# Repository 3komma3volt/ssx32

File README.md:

# ssx32
Open source servo controller
using a PIC18F46K20

software by Michael Bradley http://www.mculabs.com/projects/ssx32.html

hardware by berndp using Eagle 7.0 Freeware

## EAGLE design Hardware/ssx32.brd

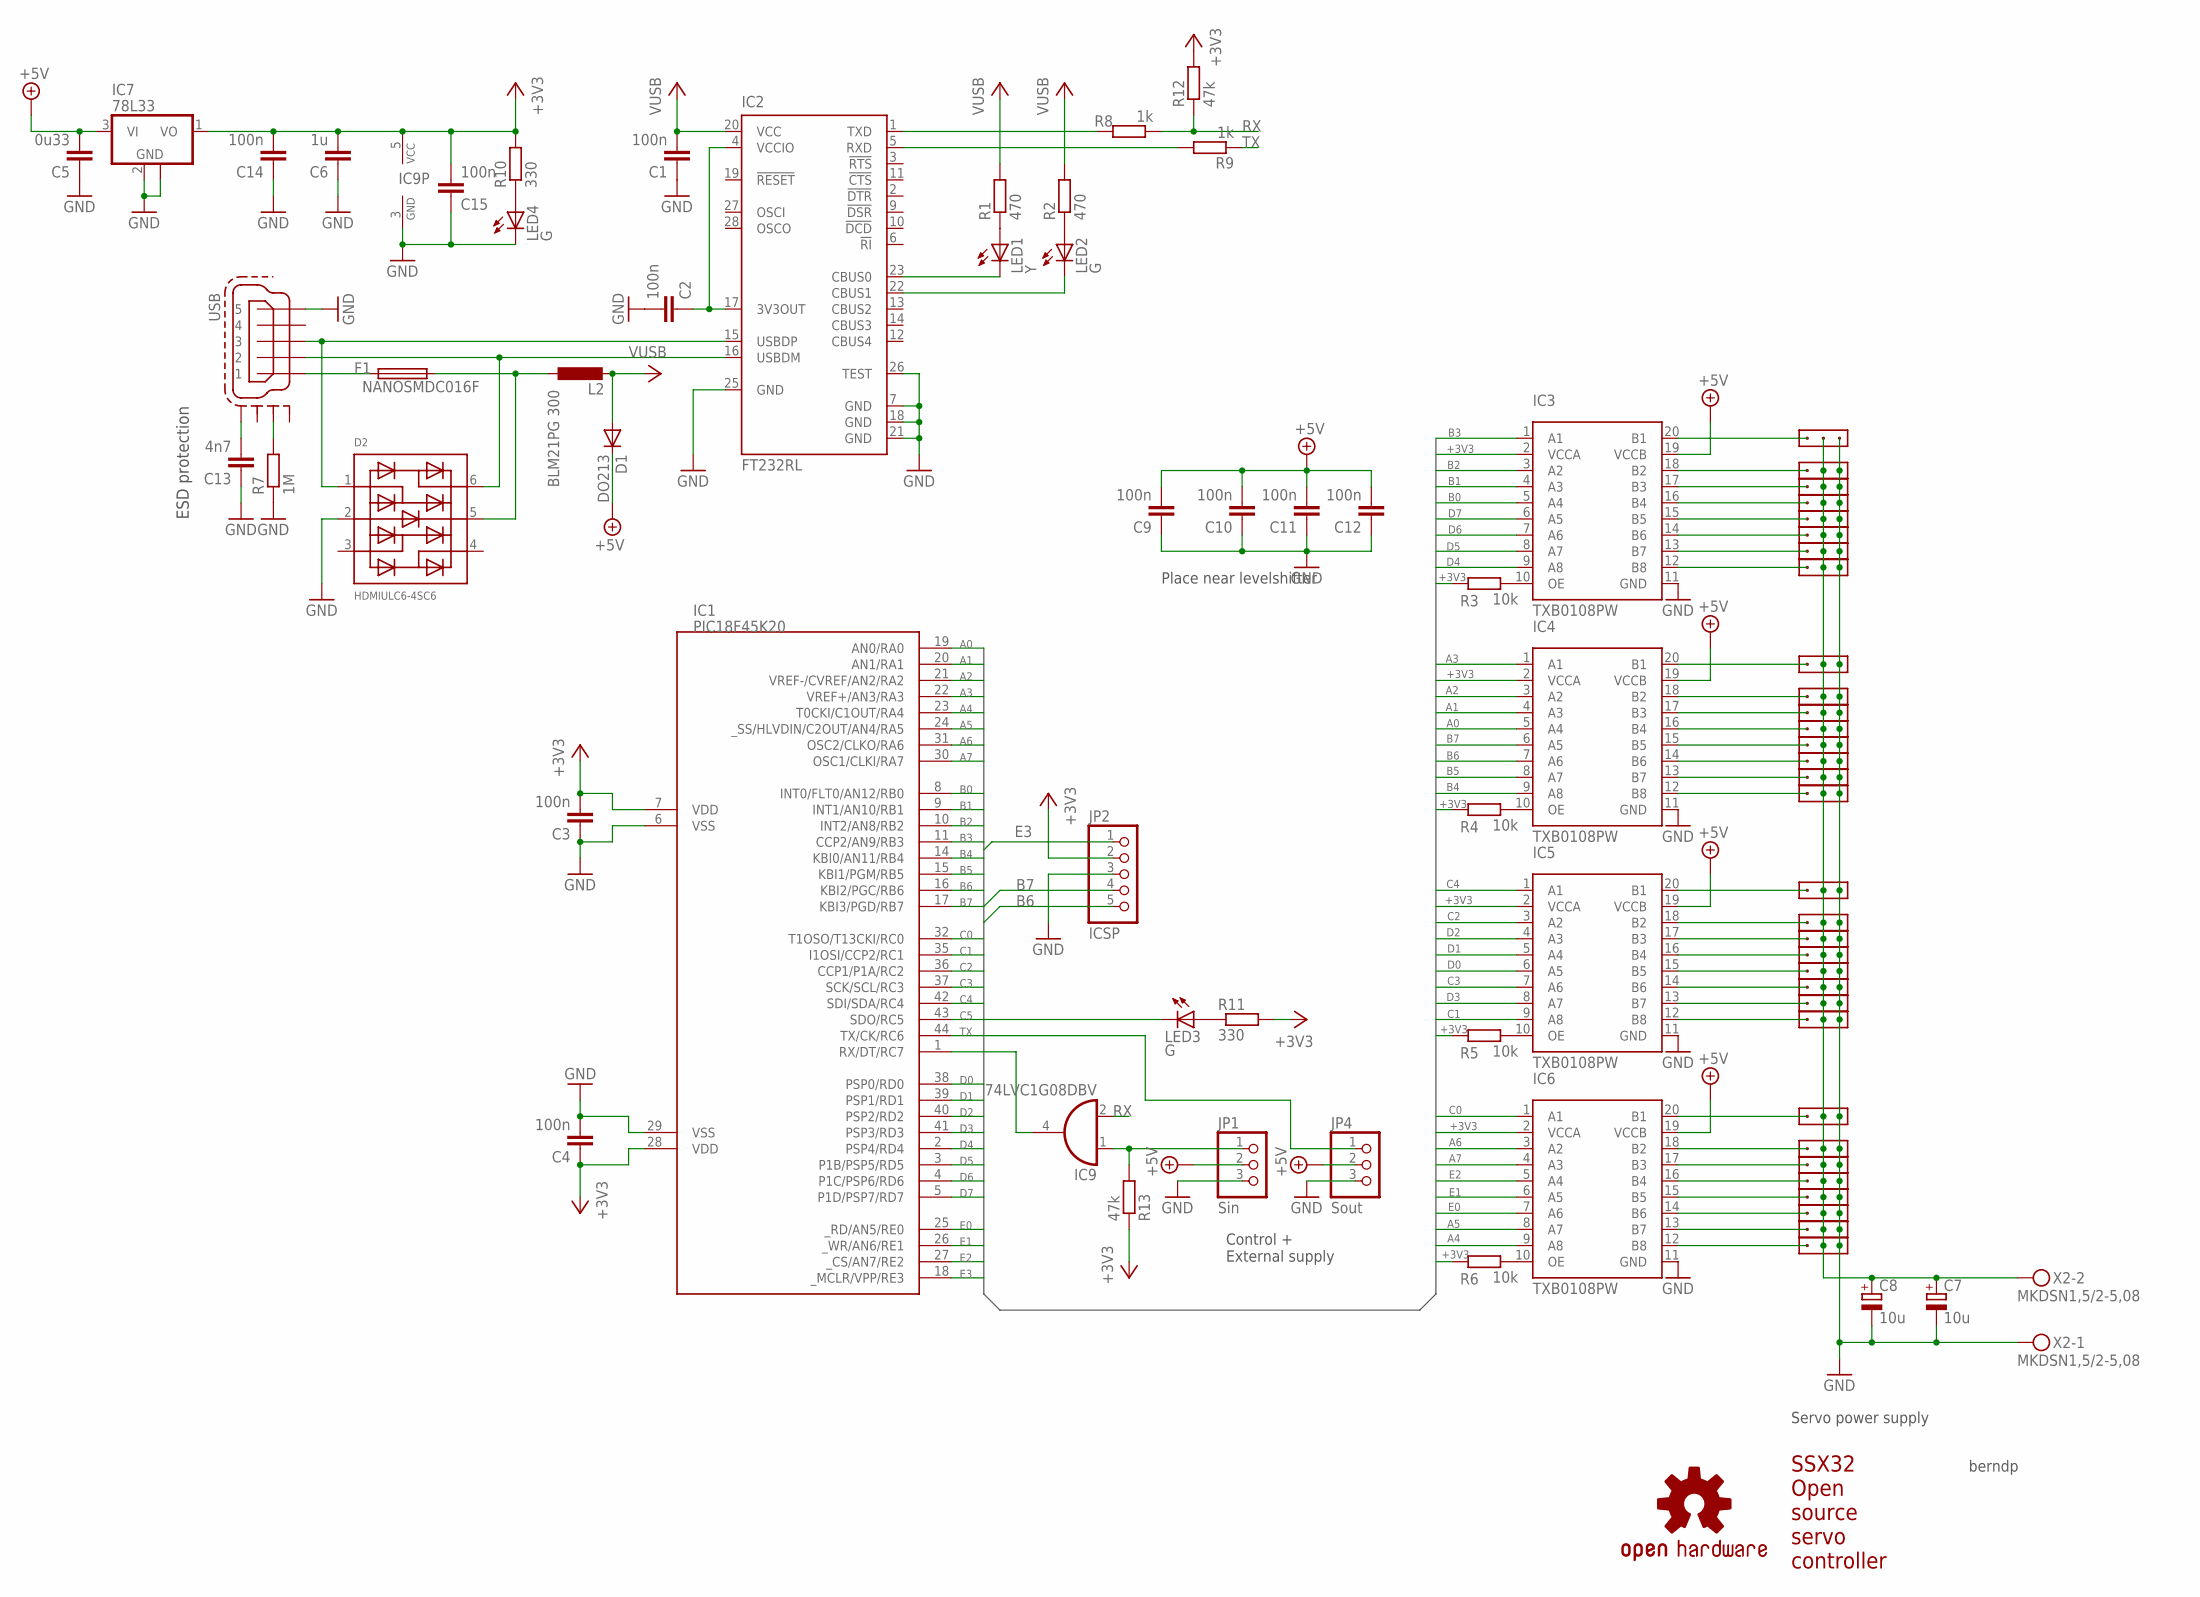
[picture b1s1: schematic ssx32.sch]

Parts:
C1, C2, C3, C4, C9, C10, C11, C12, C14, C15: 100n; C0603
C5: 0u33; C0805
C6: 1u; C0603
C7, C8: 10u; 153CLV-0505
C13: 4n7; C0603
D1: DO213; MINIMELF
D2: HDMIULC6-4SC6; SOT23-5
F1: NANOSMDC016F
IC1: PIC18F45K20; PIC18FXX20_TQFP44
IC2: FT232RL; SSOP28
IC3, IC4, IC5, IC6: TXB0108PW; PW_R-PDSO-G20
IC7: 78L33; SOT89
IC9: 74LVC1G08DBV; SOT23-5
JP1: Sin; 1X03
JP2: ICSP; 1X05
JP4: Sout; 1X03
L2: BLM21PG 300; R0805
LED1: Y; CHIPLED_0603
LED2, LED3, LED4: G; CHIPLED_0603
R1, R2: 470; R0603
R3, R4, R5, R6: 10k; R0603
R7: 1M; R0603
R8, R9: 1k; R0603
R10, R11: 330; R0603
R12, R13: 47k; R0603
U$2: OSHW-LOGOM; OSHW-LOGO-M
X1: 8; 1X3
X2: MKDSN1,5/2-5,08
X3: 17; 1X3
X4: 7; 1X3
X5: 6; 1X3
X6: 5; 1X3
X7: 4; 1X3
X8: 3; 1X3
X9: 2; 1X3
X10: 1; 1X3
X11: 19; 1X3
X12: 16; 1X3
X13: 15; 1X3
X14: 14; 1X3
X15: 13; 1X3
X16: 12; 1X3
X17: 11; 1X3
X18: 10; 1X3
X19: 9; 1X3
X20: 20; 1X3
X21: 21; 1X3
X22: 22; 1X3
X23: 23; 1X3
X24: 24; 1X3
X25: 25; 1X3
X26: 26; 1X3
X27: 27; 1X3
X28: 28; 1X3
X29: 29; 1X3
X30: 30; 1X3
X31: 31; 1X3
X32: 32; 1X3
X34: 18; 1X3
X35: USB; 32005-301

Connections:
+3V3: C3.2, C4.1, C6.2, C14.2, C15.2, IC1.7 (VDD), IC1.28 (VDD), IC3.2 (VCCA), IC4.2 (VCCA), IC5.2 (VCCA), IC6.2 (VCCA), IC7.1 (VO), IC9.5 (VCC), JP2.2, R3.1, R4.1, R5.1, R6.1, R10.2, R11.2, R12.2, R13.1
+5V: C1.2, D1.A, IC2.20 (VCC), L2.2, R1.2, R2.2
+UB: C5.2, C9.2, C10.2, C11.2, C12.2, D1.C, IC3.19 (VCCB), IC4.19 (VCCB), IC5.19 (VCCB), IC6.19 (VCCB), IC7.3 (VI), JP1.2, JP4.2
A0: IC1.19 (AN0/RA0), IC4.5 (A4)
A1: IC1.20 (AN1/RA1), IC4.4 (A3)
A2: IC1.21 (VREF-/CVREF/AN2/RA2), IC4.3 (A2)
A3: IC1.22 (VREF+/AN3/RA3), IC4.1 (A1)
A4: IC1.23 (T0CKI/C1OUT/RA4), IC6.9 (A8)
A5: IC1.24 (_SS/HLVDIN/C2OUT/AN4/RA5), IC6.8 (A7)
A6: IC1.31 (OSC2/CLKO/RA6), IC6.3 (A2)
A7: IC1.30 (OSC1/CLKI/RA7), IC6.4 (A3)
B0: IC1.8 (INT0/FLT0/AN12/RB0), IC3.5 (A4)
B1: IC1.9 (INT1/AN10/RB1), IC3.4 (A3)
B2: IC1.10 (INT2/AN8/RB2), IC3.3 (A2)
B3: IC1.11 (CCP2/AN9/RB3), IC3.1 (A1)
B4: IC1.14 (KBI0/AN11/RB4), IC4.9 (A8)
B5: IC1.15 (KBI1/PGM/RB5), IC4.8 (A7)
B6: IC1.16 (KBI2/PGC/RB6), IC4.7 (A6), JP2.5
B7: IC1.17 (KBI3/PGD/RB7), IC4.6 (A5), JP2.4
C0: IC1.32 (T1OSO/T13CKI/RC0), IC6.1 (A1)
C1: IC1.35 (I1OSI/CCP2/RC1), IC5.9 (A8)
C2: IC1.36 (CCP1/P1A/RC2), IC5.8 (A7)
C3: IC1.37 (SCK/SCL/RC3), IC5.7 (A6)
C4: IC1.42 (SDI/SDA/RC4), IC5.1 (A1)
C5: IC1.43 (SDO/RC5), LED3.C
D0: IC1.38 (PSP0/RD0), IC5.6 (A5)
D1: IC1.39 (PSP1/RD1), IC5.5 (A4)
D2: IC1.40 (PSP2/RD2), IC5.4 (A3)
D3: IC1.41 (PSP3/RD3), IC5.3 (A2)
D4: IC1.2 (PSP4/RD4), IC3.9 (A8)
D5: IC1.3 (P1B/PSP5/RD5), IC3.8 (A7)
D6: IC1.4 (P1C/PSP6/RD6), IC3.7 (A6)
D7: IC1.5 (P1D/PSP7/RD7), IC3.6 (A5)
E0: IC1.25 (_RD/AN5/RE0), IC6.7 (A6)
E1: IC1.26 (_WR/AN6/RE1), IC6.6 (A5)
E2: IC1.27 (_CS/AN7/RE2), IC6.5 (A4)
E3: IC1.18 (_MCLR/VPP/RE3), JP2.1
GND: C1.1, C2.2, C3.1, C4.2, C5.1, C6.1, C7.-, C8.-, C9.1, C10.1, C11.1, C12.1, C13.1, C14.1, C15.1, D2.2, IC1.6 (VSS), IC1.29 (VSS), IC2.7 (GND), IC2.18 (GND), IC2.21 (GND), IC2.25 (GND), IC2.26 (TEST), IC3.11 (GND), IC4.11 (GND), IC5.11 (GND), IC6.11 (GND), IC7.2 (GND), IC7.2@1 (GND), IC9.3 (GND), JP1.3, JP2.3, JP4.3, LED4.C, R7.1, X1.P$3, X2.1, X3.P$3, X4.P$3, X5.P$3, X6.P$3, X7.P$3, X8.P$3, X9.P$3, X10.P$3, X11.P$3, X12.P$3, X13.P$3, X14.P$3, X15.P$3, X16.P$3, X17.P$3, X18.P$3, X19.P$3, X20.P$3, X21.P$3, X22.P$3, X23.P$3, X24.P$3, X25.P$3, X26.P$3, X27.P$3, X28.P$3, X29.P$3, X30.P$3, X31.P$3, X32.P$3, X34.P$3, X35.5
unnamed: D2.6, IC2.16 (USBDM), X35.2
unnamed: F1.1, X35.1
unnamed: IC2.23 (CBUS0), LED1.C
unnamed: IC2.22 (CBUS1), LED2.C
unnamed: LED1.A, R1.1
unnamed: LED2.A, R2.1
unnamed: IC3.20 (B1), X1.P$1
unnamed: IC3.10 (OE), R3.2
unnamed: IC4.10 (OE), R4.2
unnamed: IC5.10 (OE), R5.2
unnamed: IC6.10 (OE), R6.2
unnamed: IC4.18 (B2), X13.P$1
unnamed: IC3.18 (B2), X4.P$1
unnamed: IC3.17 (B3), X5.P$1
unnamed: IC3.16 (B4), X6.P$1
unnamed: IC3.15 (B5), X7.P$1
unnamed: IC3.14 (B6), X8.P$1
unnamed: IC3.13 (B7), X9.P$1
unnamed: IC3.12 (B8), X10.P$1
unnamed: IC5.17 (B3), X11.P$1
unnamed: IC4.17 (B3), X14.P$1
unnamed: IC4.16 (B4), X15.P$1
unnamed: IC4.15 (B5), X16.P$1
unnamed: IC4.14 (B6), X17.P$1
unnamed: IC4.13 (B7), X18.P$1
unnamed: IC4.12 (B8), X19.P$1
unnamed: IC5.16 (B4), X20.P$1
unnamed: IC5.15 (B5), X21.P$1
unnamed: IC5.14 (B6), X22.P$1
unnamed: IC5.13 (B7), X23.P$1
unnamed: IC5.12 (B8), X24.P$1
unnamed: IC5.20 (B1), X3.P$1
unnamed: IC4.20 (B1), X12.P$1
unnamed: IC6.16 (B4), X28.P$1
unnamed: IC6.15 (B5), X29.P$1
unnamed: IC6.14 (B6), X30.P$1
unnamed: IC6.13 (B7), X31.P$1
unnamed: IC6.12 (B8), X32.P$1
unnamed: IC6.18 (B2), X26.P$1
unnamed: IC6.17 (B3), X27.P$1
unnamed: IC6.20 (B1), X25.P$1
unnamed: IC5.18 (B2), X34.P$1
unnamed: LED3.A, R11.1
unnamed: D2.1, IC2.15 (USBDP), X35.3
unnamed: IC1.1 (RX/DT/RC7), IC9.4 (O)
unnamed: R7.2, X35.M2 (S2)
unnamed: C13.2, X35.M4 (S4)
unnamed: D2.5, F1.2, L2.1
unnamed: IC2.5 (RXD), R9.2
unnamed: IC2.1 (TXD), R8.2
unnamed: IC9.1 (I0), JP1.1, R13.2
unnamed: LED4.A, R10.1
RX: IC9.2 (I1), R8.1, R12.1
TX: IC1.44 (TX/CK/RC6), JP4.1, R9.1
VPORT: C2.1, IC2.4 (VCCIO), IC2.17 (3V3OUT)
VSERVO: C7.+, C8.+, X1.P$2, X2.2, X3.P$2, X4.P$2, X5.P$2, X6.P$2, X7.P$2, X8.P$2, X9.P$2, X10.P$2, X11.P$2, X12.P$2, X13.P$2, X14.P$2, X15.P$2, X16.P$2, X17.P$2, X18.P$2, X19.P$2, X20.P$2, X21.P$2, X22.P$2, X23.P$2, X24.P$2, X25.P$2, X26.P$2, X27.P$2, X28.P$2, X29.P$2, X30.P$2, X31.P$2, X32.P$2, X34.P$2

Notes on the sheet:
Place near levelshifter
SSX32 Open source servo controller
ESD protection
Servo power supply
berndp
Control + External supply

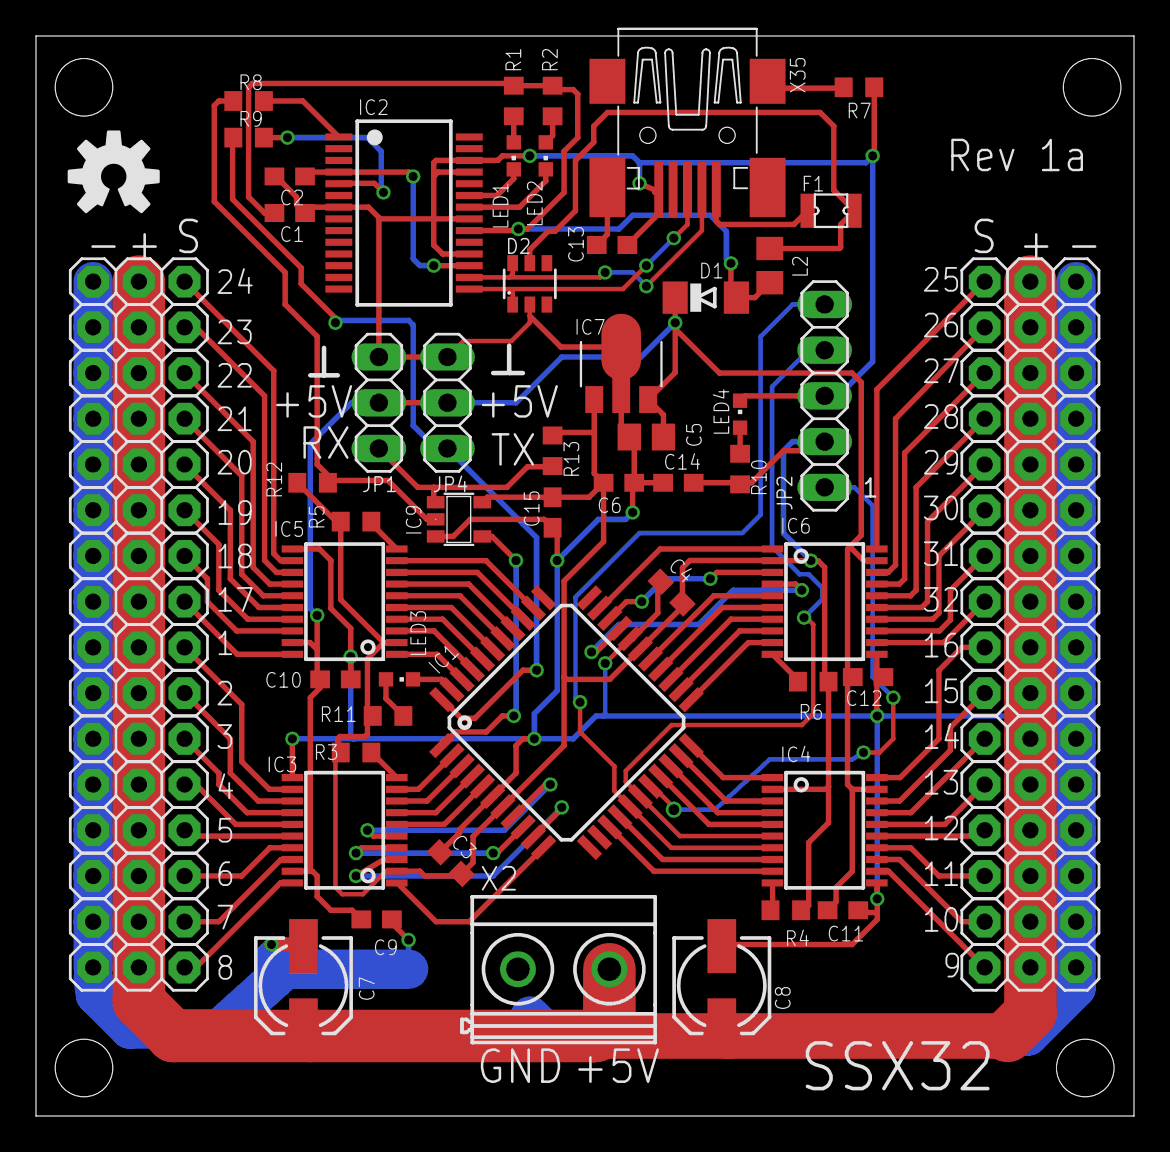
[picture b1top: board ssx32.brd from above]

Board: 2 copper layers, 61.0 x 60.0 mm, 82 parts (0 on the bottom side), 94 nets.

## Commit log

2016-03-26 Board commit
    Inital commit of PCB
    using Eagle 7
2016-03-27 Changed Board
    Added polyfuse
    Changed component values
    Replaced some components for easier PnP
2016-03-28 Error correction
    Changed missconnected PIC power supply
    Added protection for serial signals
    Changed inductors to ferrite beads
    Removed voltage select jumper
2016-04-13 Added Plane
    Added groundplane
    Increased servo VCC trace width
2016-05-11 Fixed ICSP interface
    Fixed missconnected ICSP interface
2016-05-12 Added software, minor board changes
    Added software
    Added resistor for not mounted ftdi chip
2016-06-14 Fixed schematic errors
    Added AND gate for the serial communication
    Repositioned ferrite bead
2016-06-15 Revert "Fixed schematic errors"
    This reverts commit bc55cbd2c08a143a3db725eeb6975bb6eadbf5e7.
2016-06-15 Revert "Revert "Fixed schematic errors""
    This reverts commit 02a030f20bdd3dfa1fc93a39d84e363c4da10222.
2016-06-15 Revert "Added software, minor board changes"
    This reverts commit cd959f70c37cd81d74ff6deb02d888d0a529ccba.
2016-06-15 Fixed issues
    Replaced OR with AND gate with pullups
    Removed unnecessary ferrite bead
2016-07-07 Added test software
    Added a C# application for quick tests of the servo controller
